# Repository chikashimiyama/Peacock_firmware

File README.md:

Peacock_firmware
================

The ATMega Based Peacock firmaware

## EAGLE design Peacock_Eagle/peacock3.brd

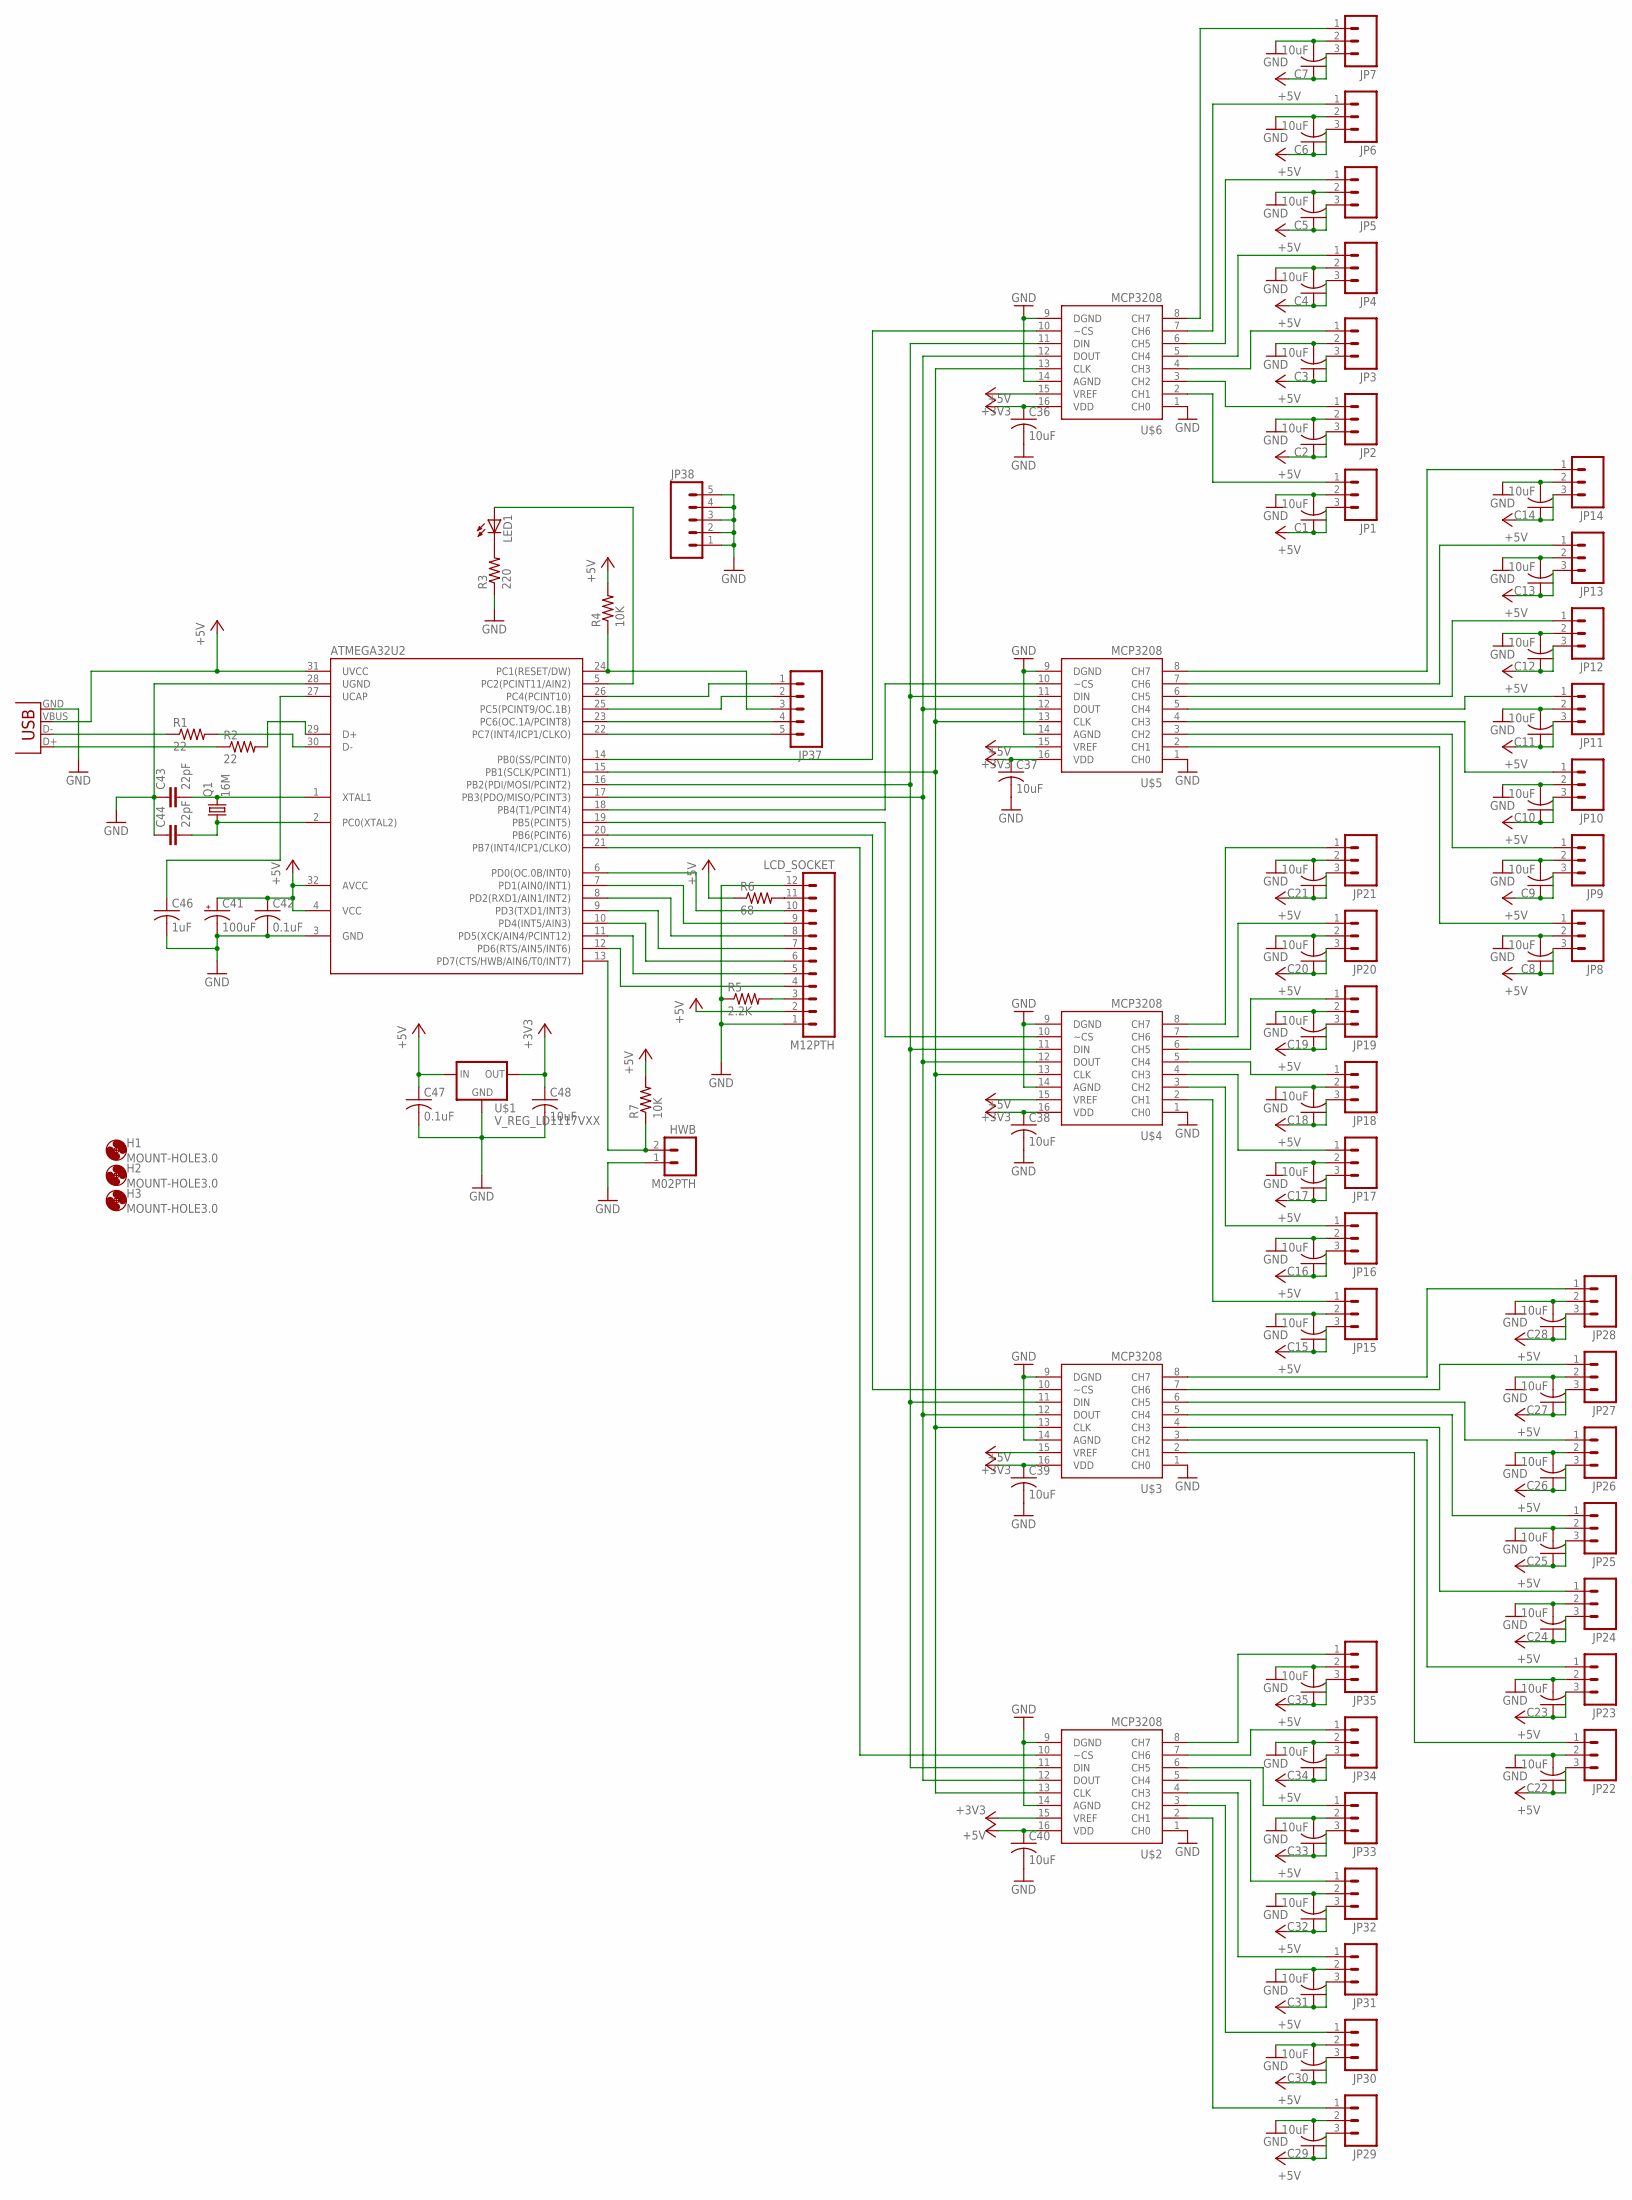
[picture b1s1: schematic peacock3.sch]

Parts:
ATMEGA32U2: ATMEGA32U2; TQFP32-08
C1, C2, C3, C4, C5, C6, C7, C8, C9, C10, C11, C12, C13, C14, C15, C16, C17, C18, C19, C20, C21, C22, C23, C24, C25, C26, C27, C28, C29, C30, C31, C32, C33, C34, C35, C36, C37, C38, C39, C40, C48: 10uF; C1210
C41: 100uF; E5-6
C42, C47: 0.1uF; C1210
C43, C44: 22pF; C050-024X044
C46: 1uF; C1210
H1, H2, H3: MOUNT-HOLE3.0; 3,0
HWB: M02PTH; 1X02
JP1, JP2, JP3, JP4, JP5, JP6, JP7, JP8, JP9, JP10, JP11, JP12, JP13, JP14, JP15, JP16, JP17, JP18, JP19, JP20, JP21, JP22, JP23, JP24, JP25, JP26, JP27, JP28, JP29, JP30, JP31, JP32, JP33, JP34, JP35: M03PTH; 1X03
JP36: USB-B; USB-B-PTH
JP37, JP38: M05PTH; 1X05
LCD_SOCKET: M12PTH; 1X12
LED1: LED5MM
Q1: 16M; HC18U-V
R1, R2: 22; 0204/7
R3: 220; 0204/7
R4, R7: 10K; 0204/7
R5: 2.2K; 0204/7
R6: 68; 0204/7
U$1: V_REG_LD1117VXX; 78XXL
U$2, U$3, U$4, U$5, U$6: MCP3208; SO16

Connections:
+3V3: C48.1, U$1.GND (OUT), U$2.15 (VREF), U$3.15 (VREF), U$4.15 (VREF), U$5.15 (VREF), U$6.15 (VREF)
+5V: ATMEGA32U2.4 (VCC), ATMEGA32U2.31 (UVCC), ATMEGA32U2.32 (AVCC), C1.1, C2.1, C3.1, C4.1, C5.1, C6.1, C7.1, C8.1, C9.1, C10.1, C11.1, C12.1, C13.1, C14.1, C15.1, C16.1, C17.1, C18.1, C19.1, C20.1, C21.1, C22.1, C23.1, C24.1, C25.1, C26.1, C27.1, C28.1, C29.1, C30.1, C31.1, C32.1, C33.1, C34.1, C35.1, C36.1, C37.1, C38.1, C39.1, C40.1, C41.+, C42.1, C47.1, JP1.3, JP2.3, JP3.3, JP4.3, JP5.3, JP6.3, JP7.3, JP8.3, JP9.3, JP10.3, JP11.3, JP12.3, JP13.3, JP14.3, JP15.3, JP16.3, JP17.3, JP18.3, JP19.3, JP20.3, JP21.3, JP22.3, JP23.3, JP24.3, JP25.3, JP26.3, JP27.3, JP28.3, JP29.3, JP30.3, JP31.3, JP32.3, JP33.3, JP34.3, JP35.3, JP36.VBUS, LCD_SOCKET.2, R4.2, R6.1, R7.2, U$1.OUT (IN), U$2.16 (VDD), U$3.16 (VDD), U$4.16 (VDD), U$5.16 (VDD), U$6.16 (VDD)
BIT0: ATMEGA32U2.9 (PD3(TXD1/INT3)), LCD_SOCKET.7
BIT1: ATMEGA32U2.8 (PD2(RXD1/AIN1/INT2)), LCD_SOCKET.8
BIT2: ATMEGA32U2.7 (PD1(AIN0/INT1)), LCD_SOCKET.9
BIT3: ATMEGA32U2.6 (PD0(OC.0B/INT0)), LCD_SOCKET.10
CLK: ATMEGA32U2.15 (PB1(SCLK/PCINT1)), U$2.13 (CLK), U$3.13 (CLK), U$4.13 (CLK), U$5.13 (CLK), U$6.13 (CLK)
ENABLE: ATMEGA32U2.10 (PD4(INT5/AIN3)), LCD_SOCKET.6
GND: ATMEGA32U2.3 (GND), ATMEGA32U2.28 (UGND), C1.2, C2.2, C3.2, C4.2, C5.2, C6.2, C7.2, C8.2, C9.2, C10.2, C11.2, C12.2, C13.2, C14.2, C15.2, C16.2, C17.2, C18.2, C19.2, C20.2, C21.2, C22.2, C23.2, C24.2, C25.2, C26.2, C27.2, C28.2, C29.2, C30.2, C31.2, C32.2, C33.2, C34.2, C35.2, C36.2, C37.2, C38.2, C39.2, C40.2, C41.-, C42.2, C43.1, C44.1, C46.2, C47.2, C48.2, HWB.1, JP1.2, JP2.2, JP3.2, JP4.2, JP5.2, JP6.2, JP7.2, JP8.2, JP9.2, JP10.2, JP11.2, JP12.2, JP13.2, JP14.2, JP15.2, JP16.2, JP17.2, JP18.2, JP19.2, JP20.2, JP21.2, JP22.2, JP23.2, JP24.2, JP25.2, JP26.2, JP27.2, JP28.2, JP29.2, JP30.2, JP31.2, JP32.2, JP33.2, JP34.2, JP35.2, JP36.GND, JP38.1, JP38.2, JP38.3, JP38.4, JP38.5, LCD_SOCKET.1, LCD_SOCKET.12, R3.1, R5.1, U$1.IN (GND), U$2.1 (CH0), U$2.9 (DGND), U$2.14 (AGND), U$3.1 (CH0), U$3.9 (DGND), U$3.14 (AGND), U$4.1 (CH0), U$4.9 (DGND), U$4.14 (AGND), U$5.1 (CH0), U$5.9 (DGND), U$5.14 (AGND), U$6.1 (CH0), U$6.9 (DGND), U$6.14 (AGND)
HWB: ATMEGA32U2.13 (PD7(CTS/HWB/AIN6/T0/INT7)), HWB.2, R7.1
MISO: ATMEGA32U2.17 (PB3(PDO/MISO/PCINT3)), U$2.12 (DOUT), U$3.12 (DOUT), U$4.12 (DOUT), U$5.12 (DOUT), U$6.12 (DOUT)
MOSI: ATMEGA32U2.16 (PB2(PDI/MOSI/PCINT2)), U$2.11 (DIN), U$3.11 (DIN), U$4.11 (DIN), U$5.11 (DIN), U$6.11 (DIN)
unnamed: ATMEGA32U2.5 (PC2(PCINT11/AIN2)), LED1.A
unnamed: JP15.1, U$4.2 (CH1)
unnamed: JP16.1, U$4.3 (CH2)
unnamed: JP17.1, U$4.4 (CH3)
unnamed: JP18.1, U$4.5 (CH4)
unnamed: JP19.1, U$4.6 (CH5)
unnamed: ATMEGA32U2.30 (D-), R1.2
unnamed: ATMEGA32U2.2 (PC0(XTAL2)), C44.2, Q1.1
unnamed: ATMEGA32U2.1 (XTAL1), C43.2, Q1.2
unnamed: JP20.1, U$4.7 (CH6)
unnamed: JP21.1, U$4.8 (CH7)
unnamed: JP1.1, U$6.2 (CH1)
unnamed: ATMEGA32U2.29 (D+), R2.2
unnamed: JP36.D+, R2.1
unnamed: JP36.D-, R1.1
unnamed: JP2.1, U$6.3 (CH2)
unnamed: LED1.K (C), R3.2
unnamed: ATMEGA32U2.26 (PC4(PCINT10)), JP37.1
unnamed: ATMEGA32U2.25 (PC5(PCINT9/OC.1B)), JP37.2
unnamed: LCD_SOCKET.3, R5.2
unnamed: JP3.1, U$6.4 (CH3)
unnamed: ATMEGA32U2.23 (PC6(OC.1A/PCINT8)), JP37.4
unnamed: LCD_SOCKET.11, R6.2
unnamed: ATMEGA32U2.27 (UCAP), C46.1
unnamed: JP4.1, U$6.5 (CH4)
unnamed: JP5.1, U$6.6 (CH5)
unnamed: JP27.1, U$3.7 (CH6)
unnamed: JP28.1, U$3.8 (CH7)
unnamed: JP35.1, U$2.8 (CH7)
unnamed: JP34.1, U$2.7 (CH6)
unnamed: JP6.1, U$6.7 (CH6)
unnamed: JP7.1, U$6.8 (CH7)
unnamed: ATMEGA32U2.14 (PB0(SS/PCINT0)), U$6.10 (~CS)
unnamed: ATMEGA32U2.21 (PB7(INT4/ICP1/CLKO)), U$2.10 (~CS)
unnamed: JP14.1, U$5.8 (CH7)
unnamed: JP13.1, U$5.7 (CH6)
unnamed: JP12.1, U$5.6 (CH5)
unnamed: ATMEGA32U2.20 (PB6(PCINT6)), U$3.10 (~CS)
unnamed: JP11.1, U$5.5 (CH4)
unnamed: JP10.1, U$5.4 (CH3)
unnamed: ATMEGA32U2.18 (PB4(T1/PCINT4)), U$5.10 (~CS)
unnamed: ATMEGA32U2.19 (PB5(PCINT5)), U$4.10 (~CS)
unnamed: JP9.1, U$5.3 (CH2)
unnamed: JP8.1, U$5.2 (CH1)
unnamed: JP25.1, U$3.5 (CH4)
unnamed: JP24.1, U$3.4 (CH3)
unnamed: JP23.1, U$3.3 (CH2)
unnamed: ATMEGA32U2.22 (PC7(INT4/ICP1/CLKO)), JP37.5
unnamed: JP22.1, U$3.2 (CH1)
unnamed: JP33.1, U$2.6 (CH5)
unnamed: JP32.1, U$2.5 (CH4)
unnamed: JP31.1, U$2.4 (CH3)
unnamed: JP30.1, U$2.3 (CH2)
unnamed: JP29.1, U$2.2 (CH1)
unnamed: JP26.1, U$3.6 (CH5)
RESET: ATMEGA32U2.24 (PC1(RESET/DW)), JP37.3, R4.1
RS: ATMEGA32U2.12 (PD6(RTS/AIN5/INT6)), LCD_SOCKET.4
RW: ATMEGA32U2.11 (PD5(XCK/AIN4/PCINT12)), LCD_SOCKET.5

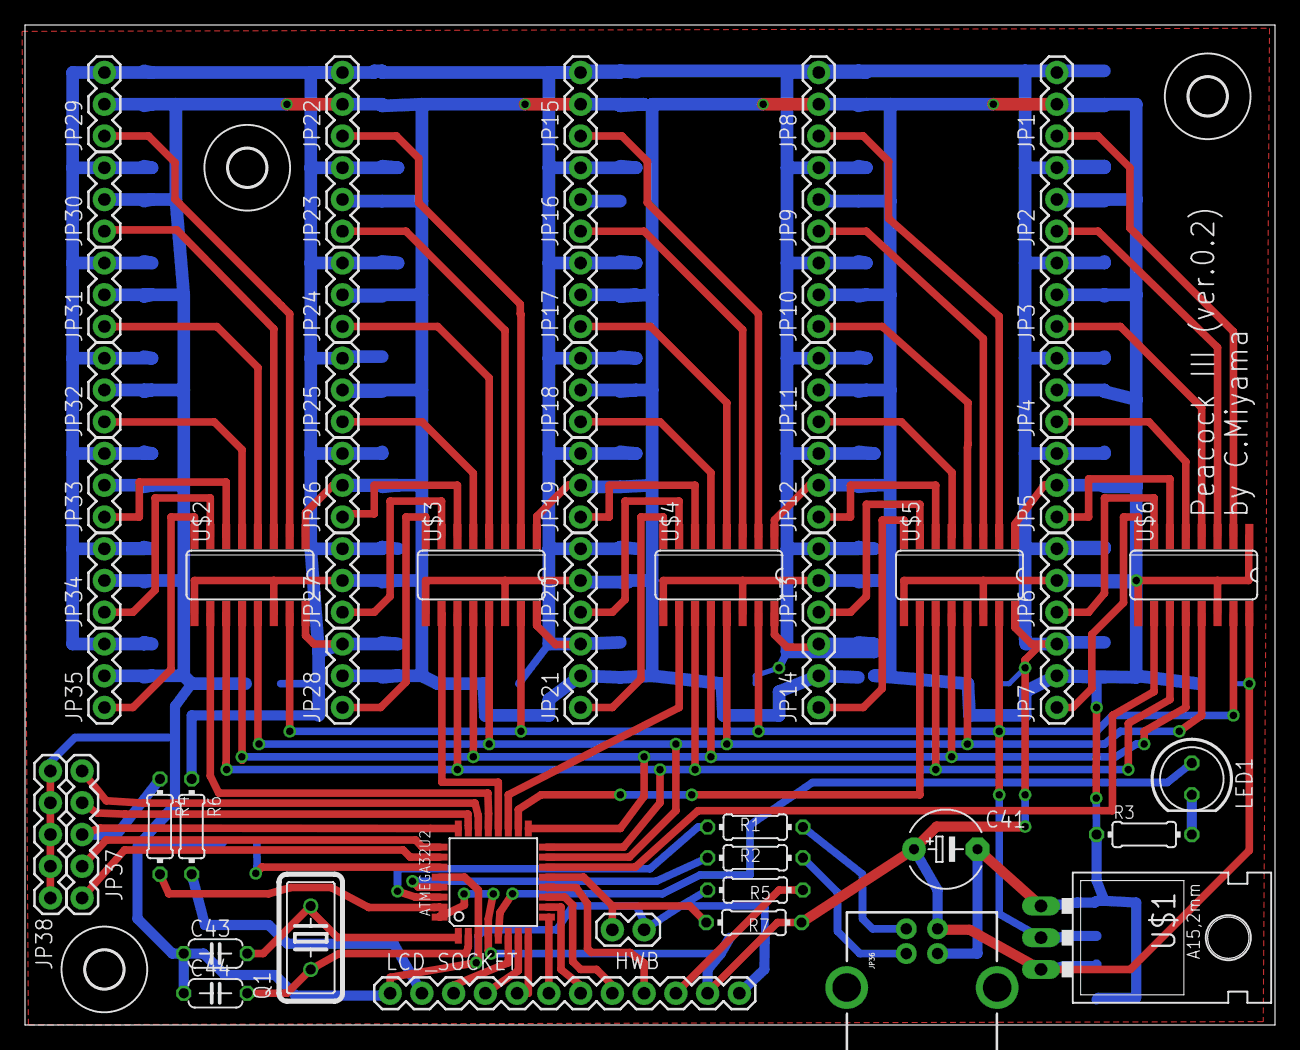
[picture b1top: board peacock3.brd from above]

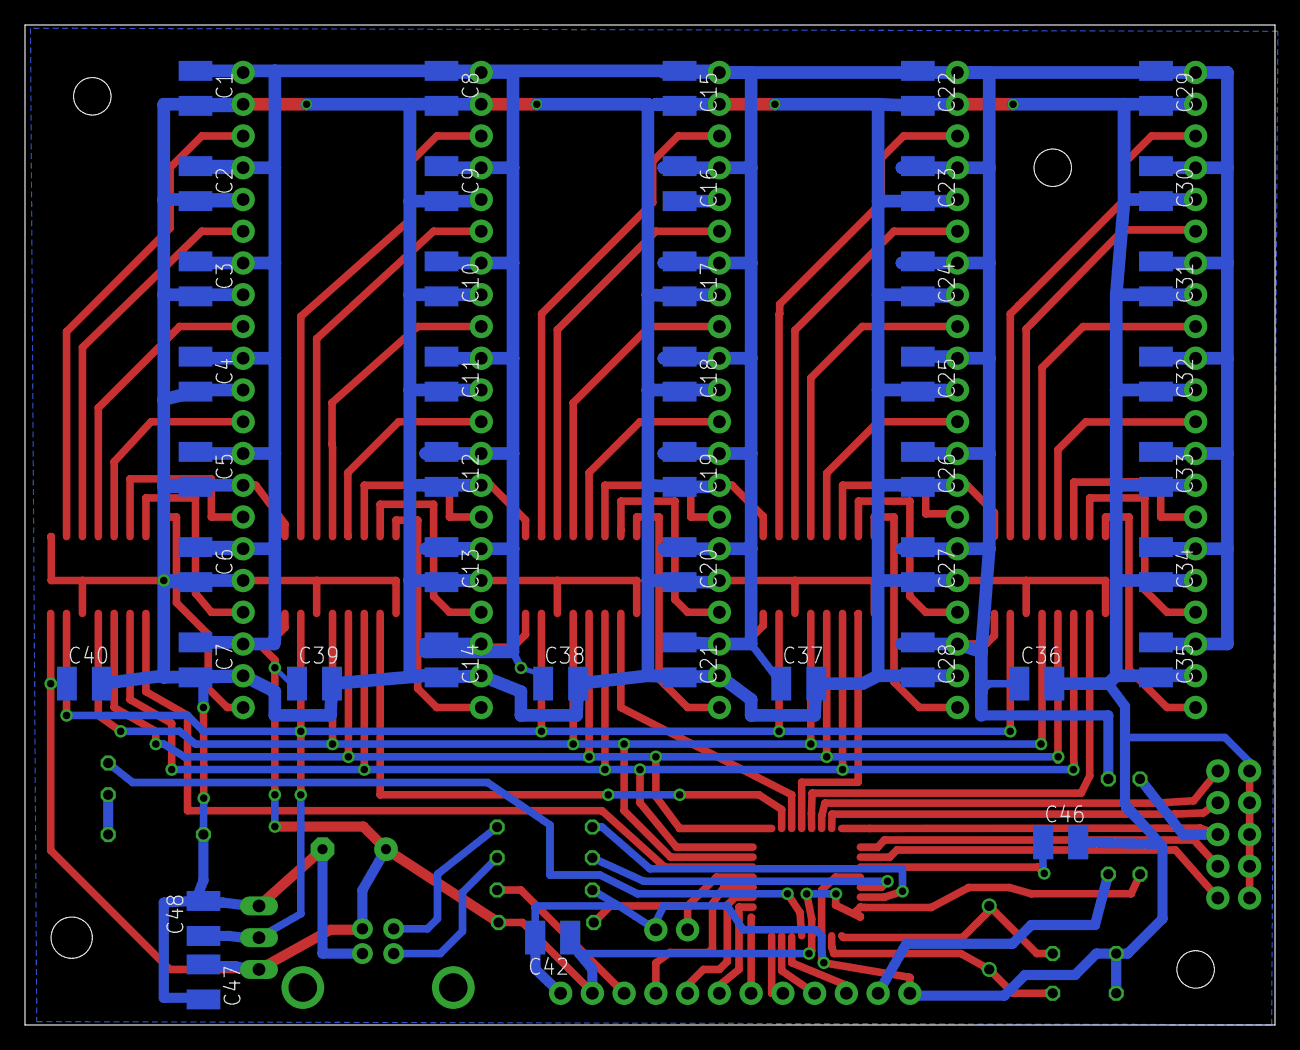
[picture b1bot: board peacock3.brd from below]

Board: 2 copper layers, 100.0 x 80.0 mm, 106 parts (44 on the bottom side), 70 nets.

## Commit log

2014-03-12 check sum implemented
2014-04-03 eagle data added
2014-04-03 schemtic fixed
2014-04-27 power update
2014-04-29 routing done
2014-05-26 peacock update
2014-05-26 added schematic again
2014-05-26 LED fixed
2014-05-28 speed up
2014-06-08 draft of paper
2014-06-08 modified
2014-06-16 test
2014-07-01 bugfix

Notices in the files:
parts and their libraries:
SparkFun-Connectors: Licensing: CC v3.0 Share-Alike You are welcome to use this library for commercial purposes.
